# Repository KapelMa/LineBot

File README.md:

# LineBot
CPE Projekt 2015/16 

HTL Saalfelden, 4.ET
Matthias, Felix

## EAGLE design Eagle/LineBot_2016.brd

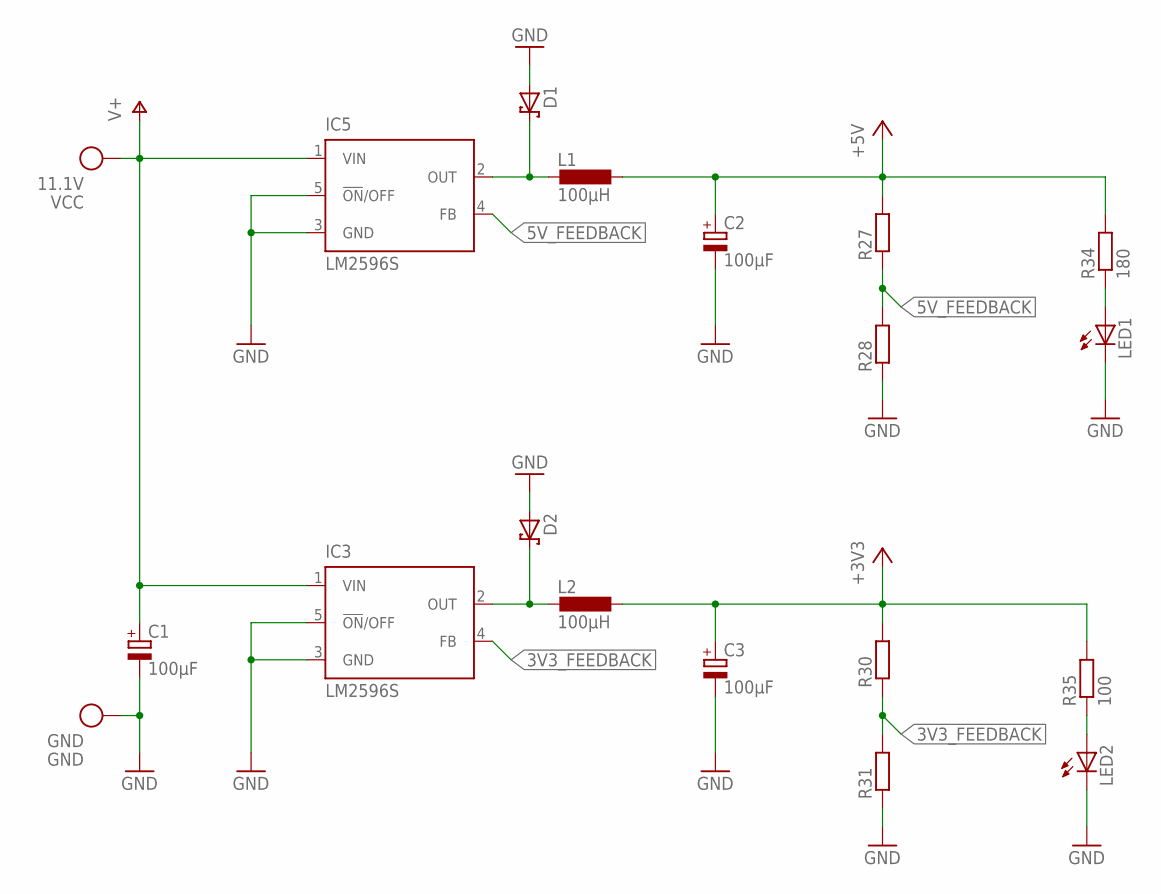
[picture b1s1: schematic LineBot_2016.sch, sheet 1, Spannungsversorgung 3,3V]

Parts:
C1: 100µF; 153CLV-1010
C2, C3: 100µF; 153CLV-0807
D1, D2: SCHOTTKY-DIODESMD; SMB
GND: GND; GOLDKONTAKT3MM
IC3, IC5: LM2596S; TO263-5
L1, L2: 100µH; MSS7341
LED1, LED2: LEDCHIPLED_0805; CHIPLED_0805
R27, R28, R30, R31: R-EU_R0805; R0805
R34: 180; R0805
R35: 100; R0805
VCC: 11.1V; GOLDKONTAKT3MM

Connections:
3V3_FEEDBACK: IC3.4 (FB), R30.1, R31.2
5V_FEEDBACK: IC5.4 (FB), R27.1, R28.2
+3V3: C3.+, L2.2, R30.2, R35.2; also elsewhere on the board
+5V: C2.+, L1.2, R27.2, R34.2; also elsewhere on the board
GND: C1.-, C2.-, C3.-, D1.A, D2.A, GND.1, IC3.3 (GND), IC3.5 (!ON!/OFF), IC5.3 (GND), IC5.5 (!ON!/OFF), LED1.C, LED2.C, R28.1, R31.1; also elsewhere on the board
unnamed: D1.C, IC5.2 (OUT), L1.1
unnamed: D2.C, IC3.2 (OUT), L2.1
unnamed: LED2.A, R35.1
unnamed: LED1.A, R34.1
V+: C1.+, IC3.1 (VIN), IC5.1 (VIN), VCC.1; also elsewhere on the board

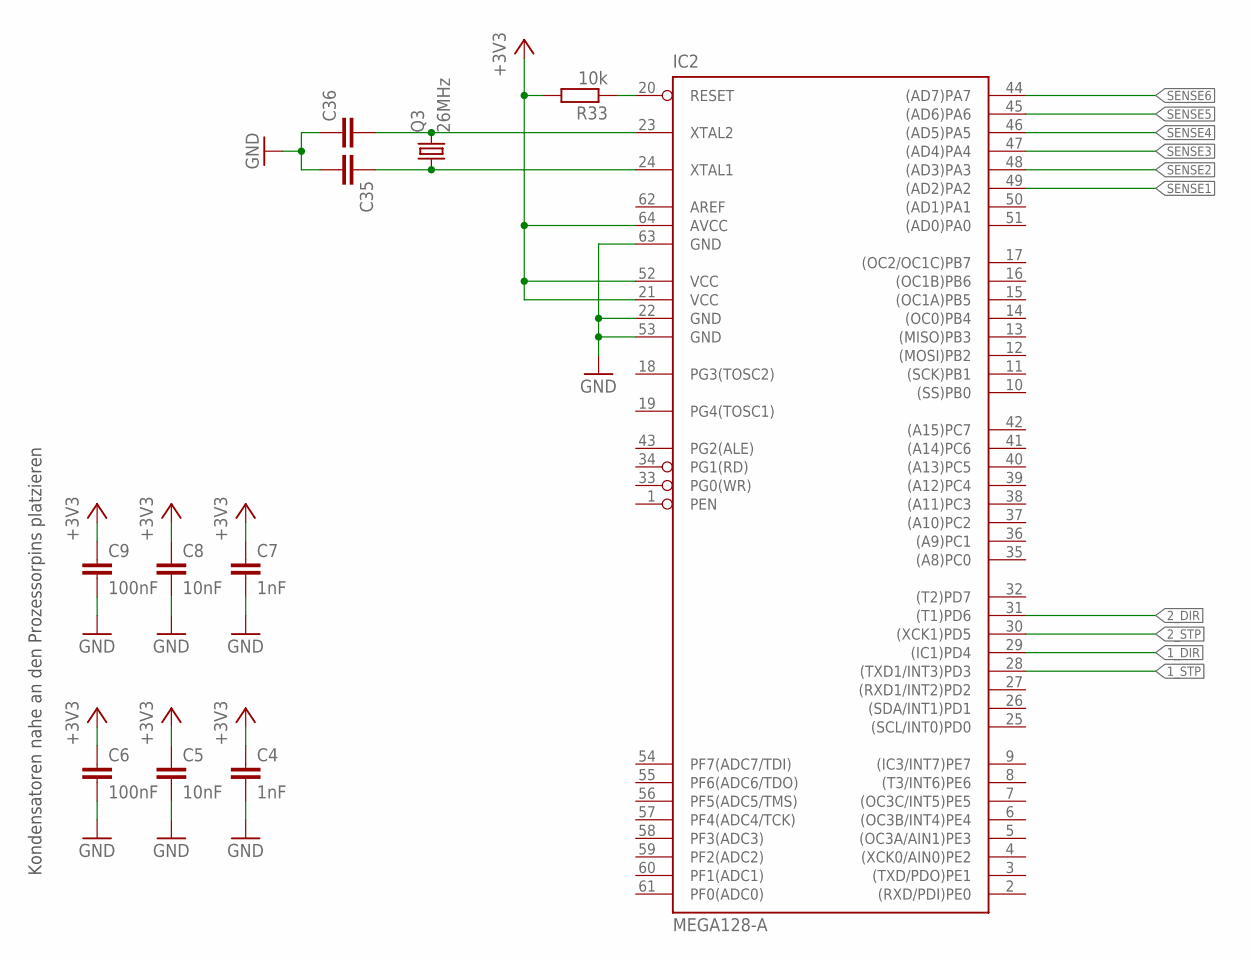
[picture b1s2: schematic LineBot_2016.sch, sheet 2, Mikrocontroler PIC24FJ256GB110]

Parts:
C4, C7: 1nF; C0805
C5, C8: 10nF; C0805
C6, C9: 100nF; C0805
C35, C36: C-EUC0805; C0805
IC2: MEGA128-A; TQFP64
Q3: 26MHz; HC49U-V
R33: 10k; R0805

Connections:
1_DIR: IC2.29 ((IC1)PD4); also elsewhere on the board
1_STP: IC2.28 ((TXD1/INT3)PD3); also elsewhere on the board
2_DIR: IC2.31 ((T1)PD6); also elsewhere on the board
2_STP: IC2.30 ((XCK1)PD5); also elsewhere on the board
+3V3: C4.1, C5.1, C6.1, C7.1, C8.1, C9.1, IC2.21 (VCC), IC2.52 (VCC), IC2.64 (AVCC), R33.2; also elsewhere on the board
GND: C4.2, C5.2, C6.2, C7.2, C8.2, C9.2, C35.2, C36.1, IC2.22 (GND), IC2.53 (GND), IC2.63 (GND); also elsewhere on the board
unnamed: IC2.20 (RESET), R33.1
unnamed: C36.2, IC2.23 (XTAL2), Q3.2
unnamed: C35.1, IC2.24 (XTAL1), Q3.1
SENSE1: IC2.49 ((AD2)PA2); also elsewhere on the board
SENSE2: IC2.48 ((AD3)PA3); also elsewhere on the board
SENSE3: IC2.47 ((AD4)PA4); also elsewhere on the board
SENSE4: IC2.46 ((AD5)PA5); also elsewhere on the board
SENSE5: IC2.45 ((AD6)PA6); also elsewhere on the board
SENSE6: IC2.44 ((AD7)PA7); also elsewhere on the board

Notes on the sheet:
Kondensatoren nahe an den Prozessorpins platzieren

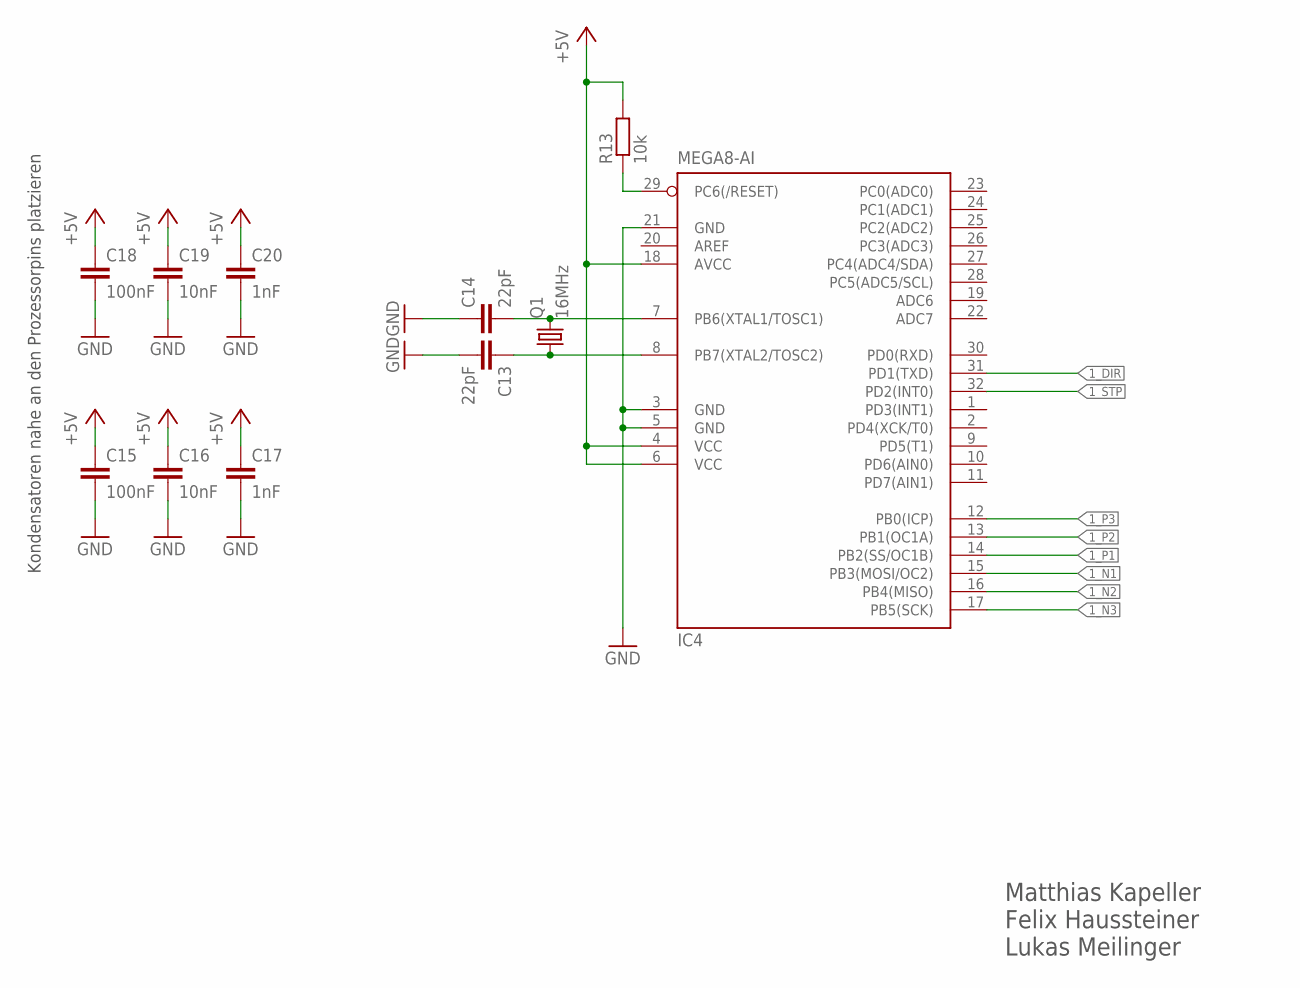
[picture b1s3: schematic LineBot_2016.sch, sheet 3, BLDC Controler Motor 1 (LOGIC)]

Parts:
C13, C14: 22pF; C0805
C15, C18: 100nF; C0805
C16, C19: 10nF; C0805
C17, C20: 1nF; C0805
IC4: MEGA8-AI; TQFP32-08
Q1: 16MHz; HC49U-V
R13: 10k; R0805

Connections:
1_DIR: IC4.31 (PD1(TXD)); also elsewhere on the board
1_N1: IC4.15 (PB3(MOSI/OC2)); also elsewhere on the board
1_N2: IC4.16 (PB4(MISO)); also elsewhere on the board
1_N3: IC4.17 (PB5(SCK)); also elsewhere on the board
1_P1: IC4.14 (PB2(SS/OC1B)); also elsewhere on the board
1_P2: IC4.13 (PB1(OC1A)); also elsewhere on the board
1_P3: IC4.12 (PB0(ICP)); also elsewhere on the board
1_STP: IC4.32 (PD2(INT0)); also elsewhere on the board
+5V: C15.1, C16.1, C17.1, C18.1, C19.1, C20.1, IC4.4 (VCC), IC4.6 (VCC), IC4.18 (AVCC), R13.2; also elsewhere on the board
GND: C13.2, C14.1, C15.2, C16.2, C17.2, C18.2, C19.2, C20.2, IC4.3 (GND), IC4.5 (GND), IC4.21 (GND); also elsewhere on the board
unnamed: C13.1, IC4.8 (PB7(XTAL2/TOSC2)), Q1.1
unnamed: C14.2, IC4.7 (PB6(XTAL1/TOSC1)), Q1.2
unnamed: IC4.29 (PC6(/RESET)), R13.1

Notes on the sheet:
Kondensatoren nahe an den Prozessorpins platzieren
Matthias Kapeller Felix Haussteiner Lukas Meilinger

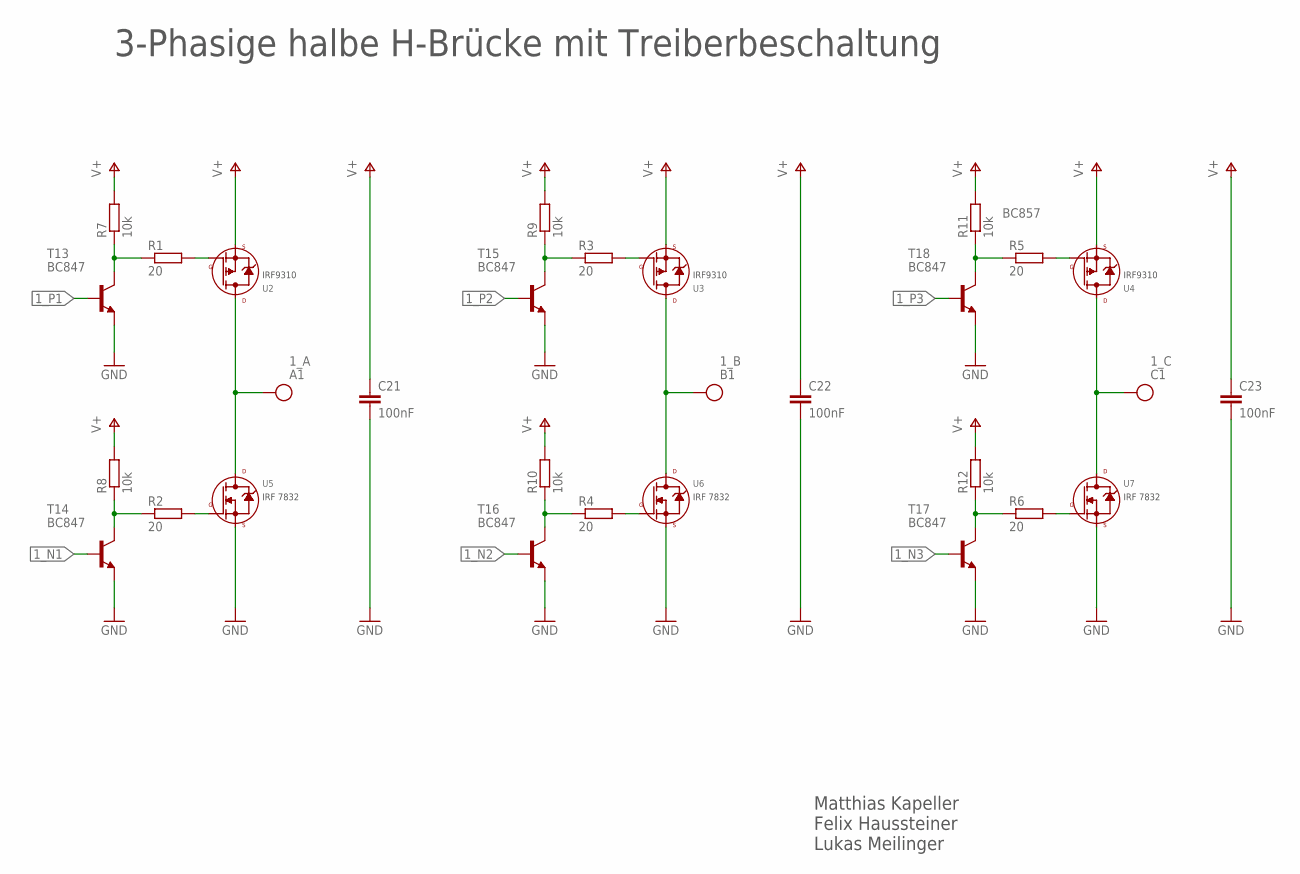
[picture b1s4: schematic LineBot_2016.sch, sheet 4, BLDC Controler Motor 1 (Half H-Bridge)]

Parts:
1_A: A1; GOLDKONTAKT3MM
1_B: B1; GOLDKONTAKT3MM
1_C: C1; GOLDKONTAKT3MM
C21, C22, C23: 100nF; C1210
R1, R2, R3, R4, R5, R6: 20; R0805
R7, R8, R9, R10, R11, R12: 10k; R0805
T13, T14, T15, T16, T17, T18: BC847; SOT23
U2, U3, U4: IRF9310; SO8
U5, U6, U7: IRF7832; SO8

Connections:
1_A: 1_A.1, U2.5 (D), U2.6# (D), U2.7 (D), U2.8 (D), U5.5 (D), U5.6# (D), U5.7 (D), U5.8 (D); also elsewhere on the board
1_B: 1_B.1, U3.5 (D), U3.6# (D), U3.7 (D), U3.8 (D), U6.5 (D), U6.6# (D), U6.7 (D), U6.8 (D); also elsewhere on the board
1_C: 1_C.1, U4.5 (D), U4.6# (D), U4.7 (D), U4.8 (D), U7.5 (D), U7.6# (D), U7.7 (D), U7.8 (D); also elsewhere on the board
1_N1: T14.1 (B); also elsewhere on the board
1_N2: T16.1 (B); also elsewhere on the board
1_N3: T17.1 (B); also elsewhere on the board
1_P1: T13.1 (B); also elsewhere on the board
1_P2: T15.1 (B); also elsewhere on the board
1_P3: T18.1 (B); also elsewhere on the board
GND: C21.2, C22.2, C23.2, T13.2 (E), T14.2 (E), T15.2 (E), T16.2 (E), T17.2 (E), T18.2 (E), U5.1 (S), U5.2 (S), U5.3 (S), U6.1 (S), U6.2 (S), U6.3 (S), U7.1 (S), U7.2 (S), U7.3 (S); also elsewhere on the board
unnamed: R1.2, U2.4 (G)
unnamed: R3.2, U3.4 (G)
unnamed: R5.2, U4.4 (G)
unnamed: R6.2, U7.4 (G)
unnamed: R4.2, U6.4 (G)
unnamed: R2.2, U5.4 (G)
N_1: R2.1, R8.1, T14.3 (C)
N_2: R4.1, R10.1, T16.3 (C)
N_3: R6.1, R12.1, T17.3 (C)
P_1: R1.1, R7.1, T13.3 (C)
P_2: R3.1, R9.1, T15.3 (C)
P_3: R5.1, R11.1, T18.3 (C)
V+: C21.1, C22.1, C23.1, R7.2, R8.2, R9.2, R10.2, R11.2, R12.2, U2.1 (S), U2.2 (S), U2.3 (S), U3.1 (S), U3.2 (S), U3.3 (S), U4.1 (S), U4.2 (S), U4.3 (S); also elsewhere on the board

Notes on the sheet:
BC857
3-Phasige halbe H-Brücke mit Treiberbeschaltung
Matthias Kapeller Felix Haussteiner Lukas Meilinger

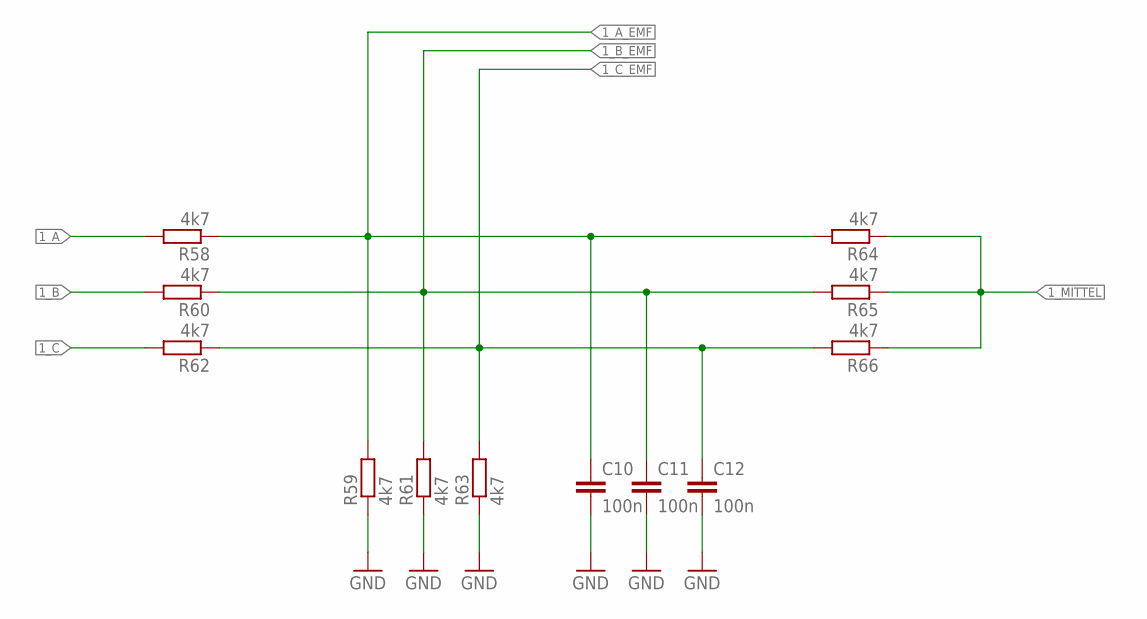
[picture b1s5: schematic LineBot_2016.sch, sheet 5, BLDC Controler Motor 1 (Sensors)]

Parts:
C10, C11, C12: 100n; C0805
R58, R59, R60, R61, R62, R63, R64, R65, R66: 4k7; R0805

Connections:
1_A: R58.2; also elsewhere on the board
1_A_EMF: C10.1, R58.1, R59.2, R64.2
1_B: R60.2; also elsewhere on the board
1_B_EMF: C11.1, R60.1, R61.2, R65.2
1_C: R62.2; also elsewhere on the board
1_C_EMF: C12.1, R62.1, R63.2, R66.2
1_MITTEL: R64.1, R65.1, R66.1
GND: C10.2, C11.2, C12.2, R59.1, R61.1, R63.1; also elsewhere on the board

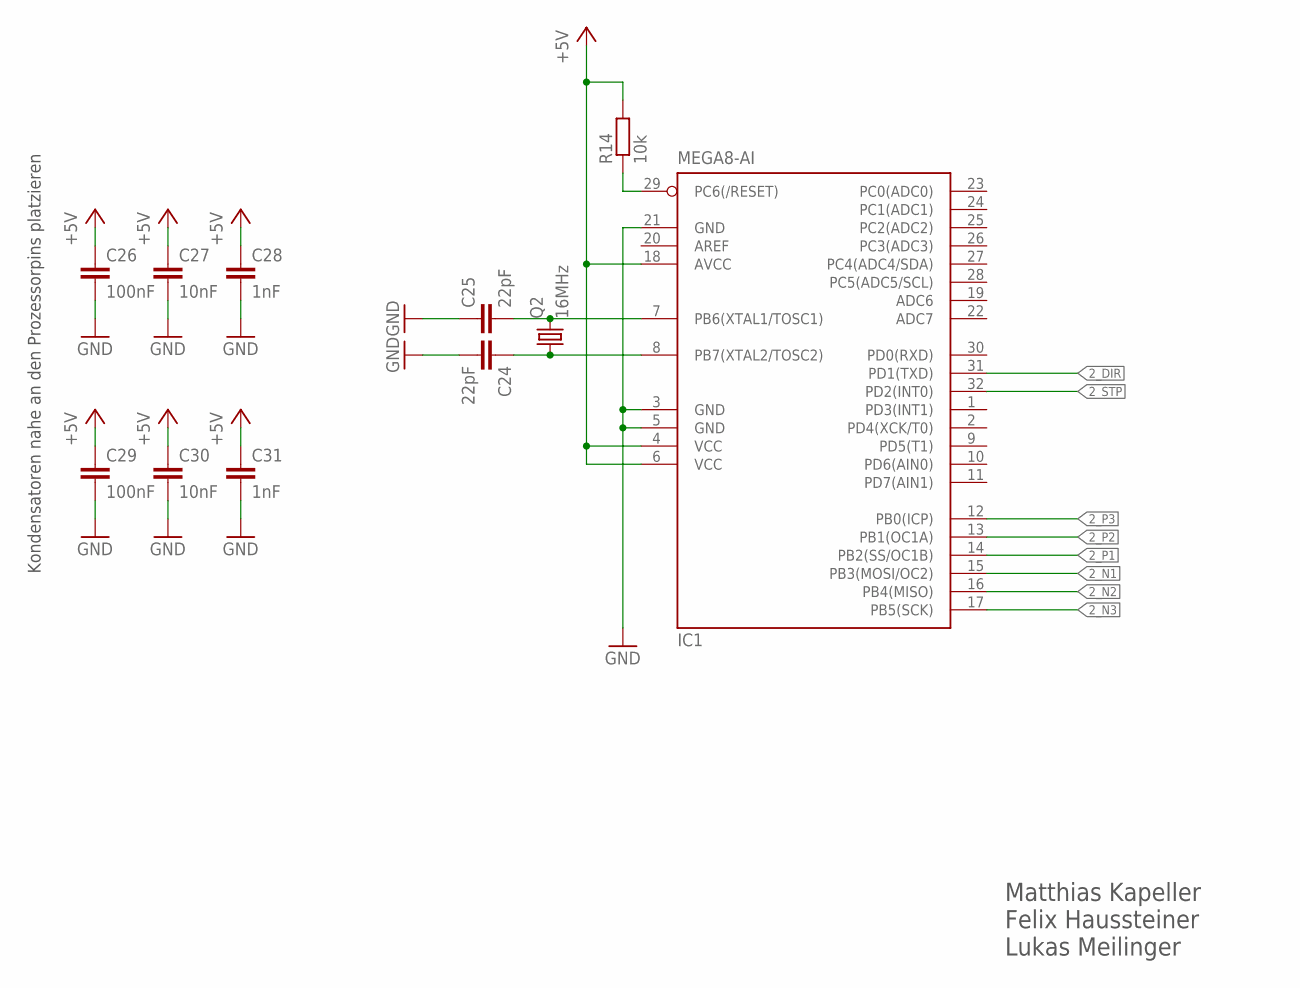
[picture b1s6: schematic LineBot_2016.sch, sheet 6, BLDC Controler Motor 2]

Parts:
C24, C25: 22pF; C0805
C26, C29: 100nF; C0805
C27, C30: 10nF; C0805
C28, C31: 1nF; C0805
IC1: MEGA8-AI; TQFP32-08
Q2: 16MHz; HC49U-V
R14: 10k; R0805

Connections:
2_DIR: IC1.31 (PD1(TXD)); also elsewhere on the board
2_N1: IC1.15 (PB3(MOSI/OC2)); also elsewhere on the board
2_N2: IC1.16 (PB4(MISO)); also elsewhere on the board
2_N3: IC1.17 (PB5(SCK)); also elsewhere on the board
2_P1: IC1.14 (PB2(SS/OC1B)); also elsewhere on the board
2_P2: IC1.13 (PB1(OC1A)); also elsewhere on the board
2_P3: IC1.12 (PB0(ICP)); also elsewhere on the board
2_STP: IC1.32 (PD2(INT0)); also elsewhere on the board
+5V: C26.1, C27.1, C28.1, C29.1, C30.1, C31.1, IC1.4 (VCC), IC1.6 (VCC), IC1.18 (AVCC), R14.2; also elsewhere on the board
GND: C24.2, C25.1, C26.2, C27.2, C28.2, C29.2, C30.2, C31.2, IC1.3 (GND), IC1.5 (GND), IC1.21 (GND); also elsewhere on the board
unnamed: C24.1, IC1.8 (PB7(XTAL2/TOSC2)), Q2.1
unnamed: C25.2, IC1.7 (PB6(XTAL1/TOSC1)), Q2.2
unnamed: IC1.29 (PC6(/RESET)), R14.1

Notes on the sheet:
Kondensatoren nahe an den Prozessorpins platzieren
Matthias Kapeller Felix Haussteiner Lukas Meilinger

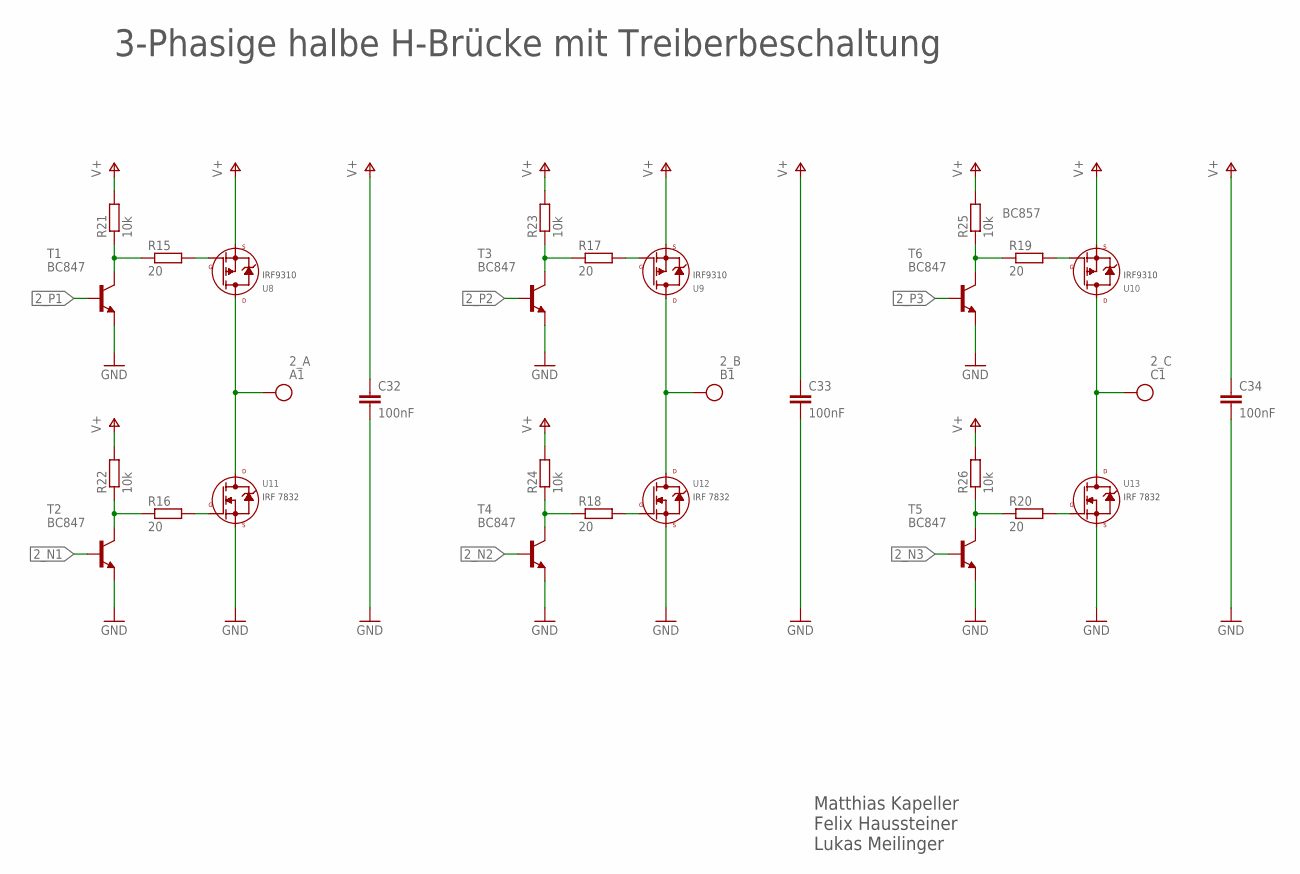
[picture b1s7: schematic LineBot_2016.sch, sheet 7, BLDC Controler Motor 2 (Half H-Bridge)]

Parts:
2_A: A1; GOLDKONTAKT3MM
2_B: B1; GOLDKONTAKT3MM
2_C: C1; GOLDKONTAKT3MM
C32, C33, C34: 100nF; C1210
R15, R16, R17, R18, R19, R20: 20; R0805
R21, R22, R23, R24, R25, R26: 10k; R0805
T1, T2, T3, T4, T5, T6: BC847; SOT23
U8, U9, U10: IRF9310; SO8
U11, U12, U13: IRF7832; SO8

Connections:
2_A: 2_A.1, U8.5 (D), U8.6# (D), U8.7 (D), U8.8 (D), U11.5 (D), U11.6# (D), U11.7 (D), U11.8 (D); also elsewhere on the board
2_B: 2_B.1, U9.5 (D), U9.6# (D), U9.7 (D), U9.8 (D), U12.5 (D), U12.6# (D), U12.7 (D), U12.8 (D); also elsewhere on the board
2_C: 2_C.1, U10.5 (D), U10.6# (D), U10.7 (D), U10.8 (D), U13.5 (D), U13.6# (D), U13.7 (D), U13.8 (D); also elsewhere on the board
2_N1: T2.1 (B); also elsewhere on the board
2_N2: T4.1 (B); also elsewhere on the board
2_N3: T5.1 (B); also elsewhere on the board
2_P1: T1.1 (B); also elsewhere on the board
2_P2: T3.1 (B); also elsewhere on the board
2_P3: T6.1 (B); also elsewhere on the board
GND: C32.2, C33.2, C34.2, T1.2 (E), T2.2 (E), T3.2 (E), T4.2 (E), T5.2 (E), T6.2 (E), U11.1 (S), U11.2 (S), U11.3 (S), U12.1 (S), U12.2 (S), U12.3 (S), U13.1 (S), U13.2 (S), U13.3 (S); also elsewhere on the board
unnamed: R15.2, U8.4 (G)
unnamed: R17.2, U9.4 (G)
unnamed: R19.2, U10.4 (G)
unnamed: R20.2, U13.4 (G)
unnamed: R18.2, U12.4 (G)
unnamed: R16.2, U11.4 (G)
N_4: R16.1, R22.1, T2.3 (C)
N_5: R18.1, R24.1, T4.3 (C)
N_6: R20.1, R26.1, T5.3 (C)
P_4: R17.1, R23.1, T3.3 (C)
P_5: R19.1, R25.1, T6.3 (C)
P_6: R15.1, R21.1, T1.3 (C)
V+: C32.1, C33.1, C34.1, R21.2, R22.2, R23.2, R24.2, R25.2, R26.2, U8.1 (S), U8.2 (S), U8.3 (S), U9.1 (S), U9.2 (S), U9.3 (S), U10.1 (S), U10.2 (S), U10.3 (S); also elsewhere on the board

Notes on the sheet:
BC857
3-Phasige halbe H-Brücke mit Treiberbeschaltung
Matthias Kapeller Felix Haussteiner Lukas Meilinger

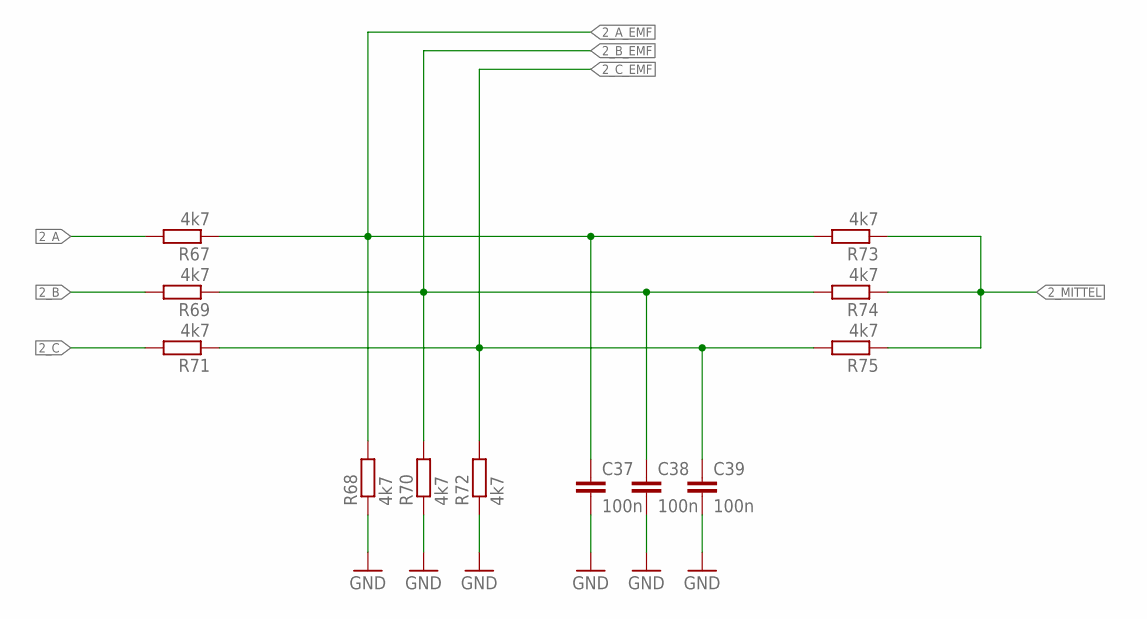
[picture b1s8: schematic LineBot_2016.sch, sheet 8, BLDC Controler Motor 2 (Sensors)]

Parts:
C37, C38, C39: 100n; C0805
R67, R68, R69, R70, R71, R72, R73, R74, R75: 4k7; R0805

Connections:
2_A: R67.2; also elsewhere on the board
2_A_EMF: C37.1, R67.1, R68.2, R73.2
2_B: R69.2; also elsewhere on the board
2_B_EMF: C38.1, R69.1, R70.2, R74.2
2_C: R71.2; also elsewhere on the board
2_C_EMF: C39.1, R71.1, R72.2, R75.2
2_MITTEL: R73.1, R74.1, R75.1
GND: C37.2, C38.2, C39.2, R68.1, R70.1, R72.1; also elsewhere on the board

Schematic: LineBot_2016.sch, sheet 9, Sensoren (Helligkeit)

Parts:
LED3, LED4, LED5, LED6, LED7, LED8: LEDKA-3528ASYC; KA-3528ASYC
LED9, LED10, LED11, LED12, LED13, LED14: LEDCHIP-LED0805; CHIP-LED0805
PH1, PH2, PH3, PH4, PH5, PH6: LEDKA-3528ASYC; KA-3528ASYC
R29, R32, R36, R37, R38, R39, R52, R53, R54, R55, R56, R57: 100; R0805
R40, R41, R42, R43, R44, R45, R46, R47, R48, R49, R50, R51: R-EU_R0805; R0805

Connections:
+3V3: R29.2, R32.2, R36.2, R37.2, R38.2, R39.2, R40.2, R41.2, R42.2, R43.2, R44.2, R45.2; also elsewhere on the board
GND: LED3.C, LED4.C, LED5.C, LED6.C, LED7.C, LED8.C, R46.1, R47.1, R48.1, R49.1, R50.1, R51.1, R52.1, R53.1, R54.1, R55.1, R56.1, R57.1; also elsewhere on the board
unnamed: LED3.A, R29.1
unnamed: LED4.A, R32.1
unnamed: LED5.A, R36.1
unnamed: LED6.A, R37.1
unnamed: LED7.A, R38.1
unnamed: LED8.A, R39.1
unnamed: PH1.A, R40.1
unnamed: PH2.A, R41.1
unnamed: PH3.A, R42.1
unnamed: PH4.A, R43.1
unnamed: PH5.A, R44.1
unnamed: PH6.A, R45.1
unnamed: LED9.C, R52.2
unnamed: LED10.C, R53.2
unnamed: LED11.C, R54.2
unnamed: LED12.C, R55.2
unnamed: LED13.C, R56.2
unnamed: LED14.C, R57.2
SENSE1: PH1.C, R46.2; also elsewhere on the board
SENSE1_ON: LED9.A
SENSE2: PH2.C, R47.2; also elsewhere on the board
SENSE2_ON: LED10.A
SENSE3: PH3.C, R48.2; also elsewhere on the board
SENSE3_ON: LED11.A
SENSE4: PH4.C, R49.2; also elsewhere on the board
SENSE4_ON: LED12.A
SENSE5: PH5.C, R50.2; also elsewhere on the board
SENSE5_ON: LED13.A
SENSE6: PH6.C, R51.2; also elsewhere on the board
SENSE6_ON: LED14.A

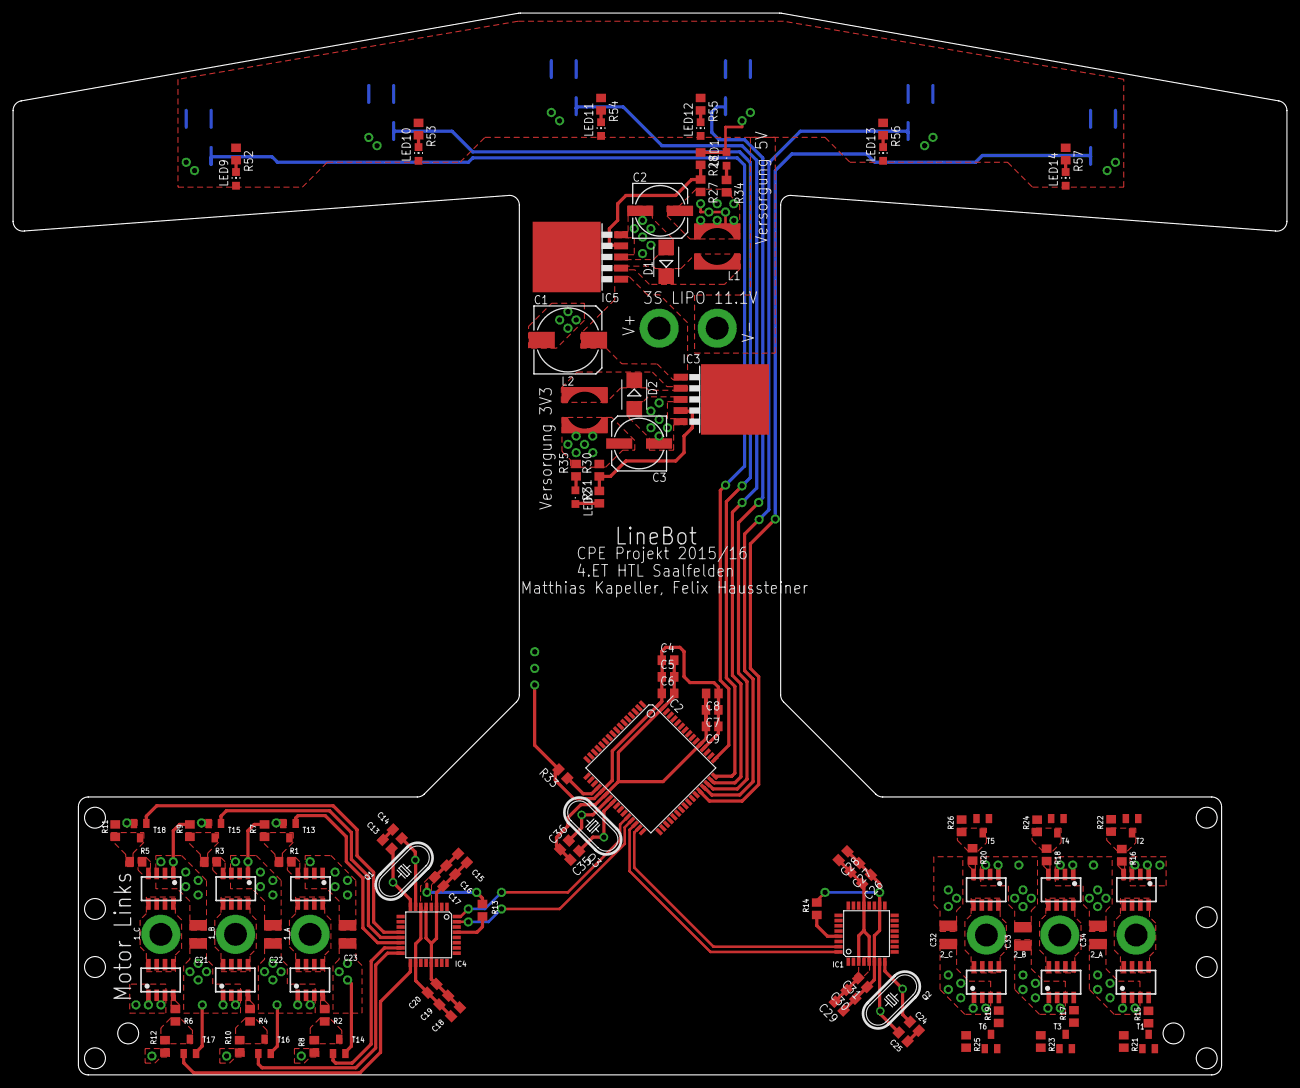
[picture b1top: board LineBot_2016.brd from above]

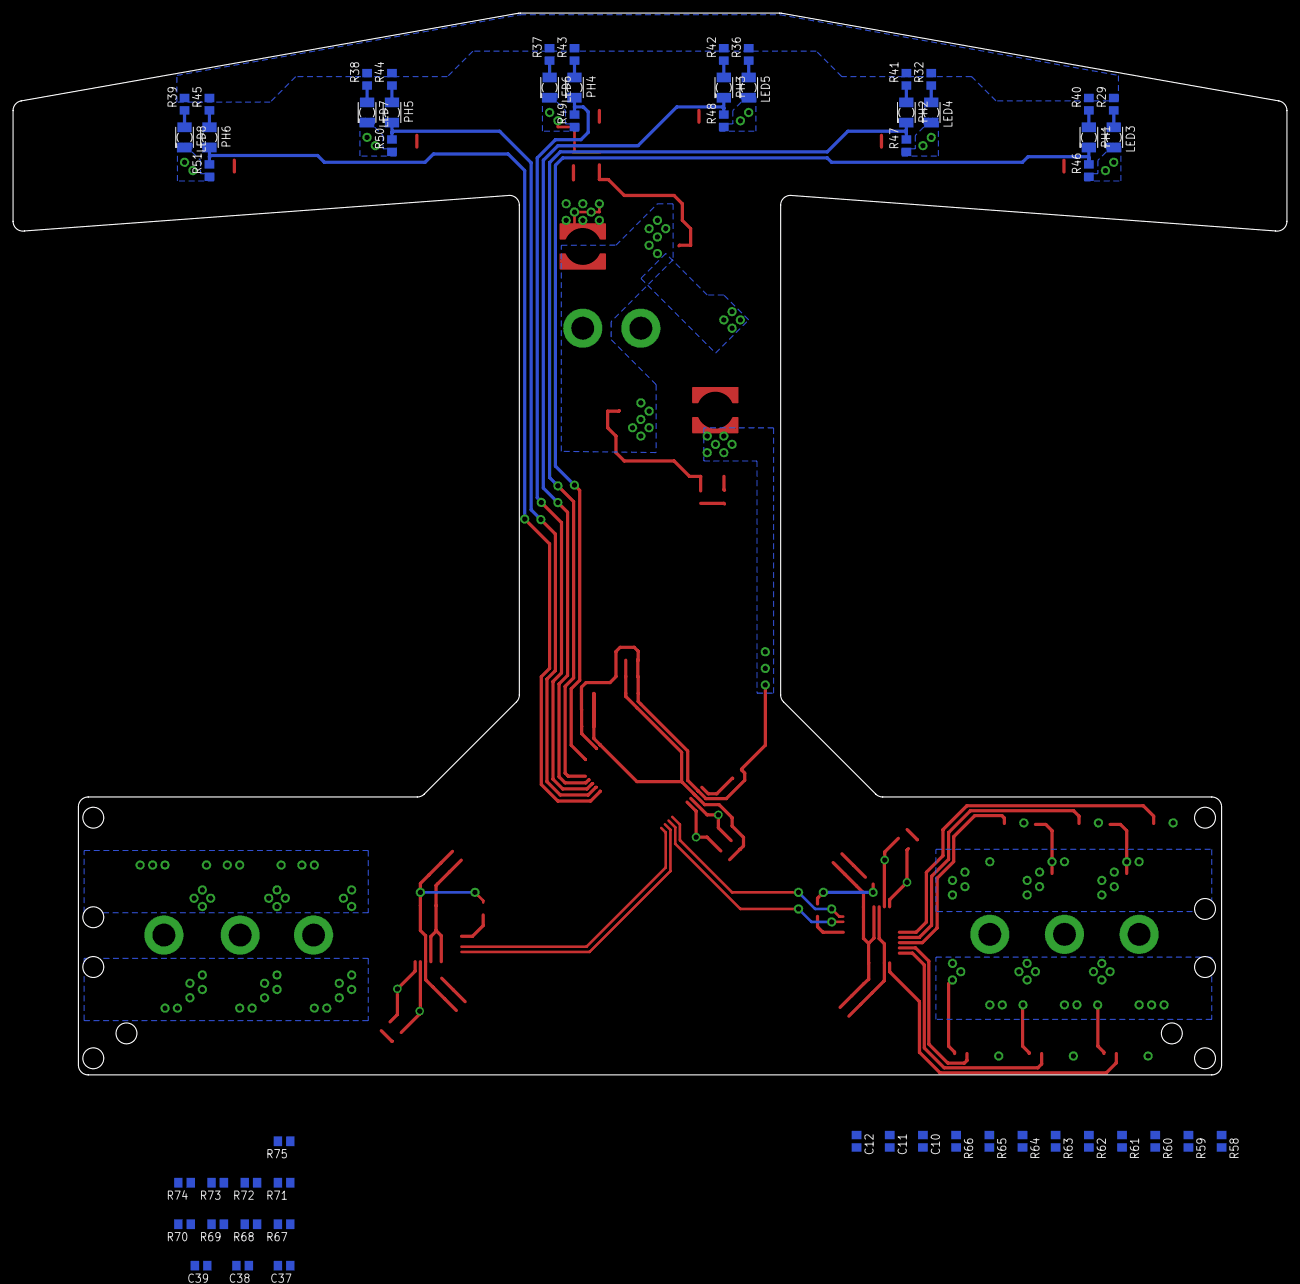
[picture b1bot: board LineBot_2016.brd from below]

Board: 4 copper layers, 195.0 x 162.5 mm, 178 parts (54 on the bottom side), 97 nets.

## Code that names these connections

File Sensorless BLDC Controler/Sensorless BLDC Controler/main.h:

/*
 * main.h
 *
 * Created: 01.06.2016 10:59:43
 *  Author: Matthias Kapeller
 */ 


#ifndef MAIN_H_
#define MAIN_H_

void AVRinit(void);

#define Motor_Up	PB0
#define Motor_Vp	PB1
#define Motor_Wp	PB2
#define Motor_Un	PB3
#define Motor_Vn	PB4
#define Motor_Wn	PB5


#define RotationDIR	PD1
#define RotationCLK	PD2


#endif /* MAIN_H_ */

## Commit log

2016-06-20 BLDC Controller Source Code
    Add Source Code Project
2016-06-20 Eagle PCB Files
    PCB Layout and Circuit sheets
2016-06-20 Sensorless BLDC Controler
    changed nothing
2016-06-21 Sensorless BLDC Controler
